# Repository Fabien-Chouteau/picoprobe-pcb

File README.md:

# picoprobe-pcb

If like me you love the Raspberry Pi Pico/RP2040, but your are not satisfied
with the available hardware debugging solution, this kit is for you ^^

This PCB is designed to turn a Pico into a nice debug probe using the
[PicoProbe software](https://github.com/raspberrypi/picoprobe).

Available at:

# Usage

## Mounting options

There are two ways to mount a Raspberry Pi Pico on the Picoprobe-PCB. You can
either solder it directly for a slim/compact result (right), or use header to
be able to re-use the Pico on other projects (left).

## Install the Picoprobe software

 1. Either get the picoprobe `.uf2` binary from our release [here](https://github.com/Fabien-Chouteau/picoprobe-pcb/releases/tag/v1.0) or compile
 it yourself from sources [here](https://github.com/raspberrypi/picoprobe).

 1. Hold the BOOTSEL button on the Pico, then connect to your computer using a
 micro USB cable.

 1. Drag and drop the UF2 file on to the RPI-RP2 drive.

 1. You should be good to go.

### Plug the picoprobe SWD pin to the Pico that you want to debug

### Build Raspberry Pi's openocd

```console
$ sudo apt install automake autoconf build-essential texinfo libtool libftdi-dev libusb-1.0-0-dev
$ git clone https://github.com/raspberrypi/openocd.git --branch picoprobe --depth=1 --no-single-branch
$ cd openocd
$ ./bootstrap
$ ./configure --enable-picoprobe
$ make -j4
```

### Run openocd

```console
$ ./src/openocd  -s tcl -f interface/picoprobe.cfg -f target/rp2040.cfg
Open On-Chip Debugger 0.10.0+dev-g18b4c35-dirty (2021-10-16-16:51)
Licensed under GNU GPL v2
For bug reports, read
        http://openocd.org/doc/doxygen/bugs.html
Info : only one transport option; autoselect 'swd'
Warn : Transport "swd" was already selected
adapter speed: 5000 kHz

Info : Hardware thread awareness created
Info : Hardware thread awareness created
Info : RP2040 Flash Bank Command
Info : Listening on port 6666 for tcl connections
Info : Listening on port 4444 for telnet connections
Info : clock speed 5000 kHz
Info : SWD DPIDR 0x0bc12477
Info : SWD DLPIDR 0x00000001
Info : SWD DPIDR 0x0bc12477
Info : SWD DLPIDR 0x10000001
Info : rp2040.core0: hardware has 4 breakpoints, 2 watchpoints
Info : rp2040.core1: hardware has 4 breakpoints, 2 watchpoints
Info : starting gdb server for rp2040.core0 on 3333
Info : Listening on port 3333 for gdb connections
Info : accepting 'gdb' connection on tcp/3333
Warn : target was in unknown state when halt was requested
target halted due to debug-request, current mode: Thread 
xPSR: 0x21000000 pc: 0x10008f64 msp: 0x20041fc0
Info : RP2040 B0 Flash Probe: 2097152 bytes @10000000, in 512 sectors
[...]
```

### Debug!

Now that openocd is connected, you can start debugging with GDB for instance.

```console
$ arm-eabi-none-gdb
(gdb) target extended-remote :3333
```

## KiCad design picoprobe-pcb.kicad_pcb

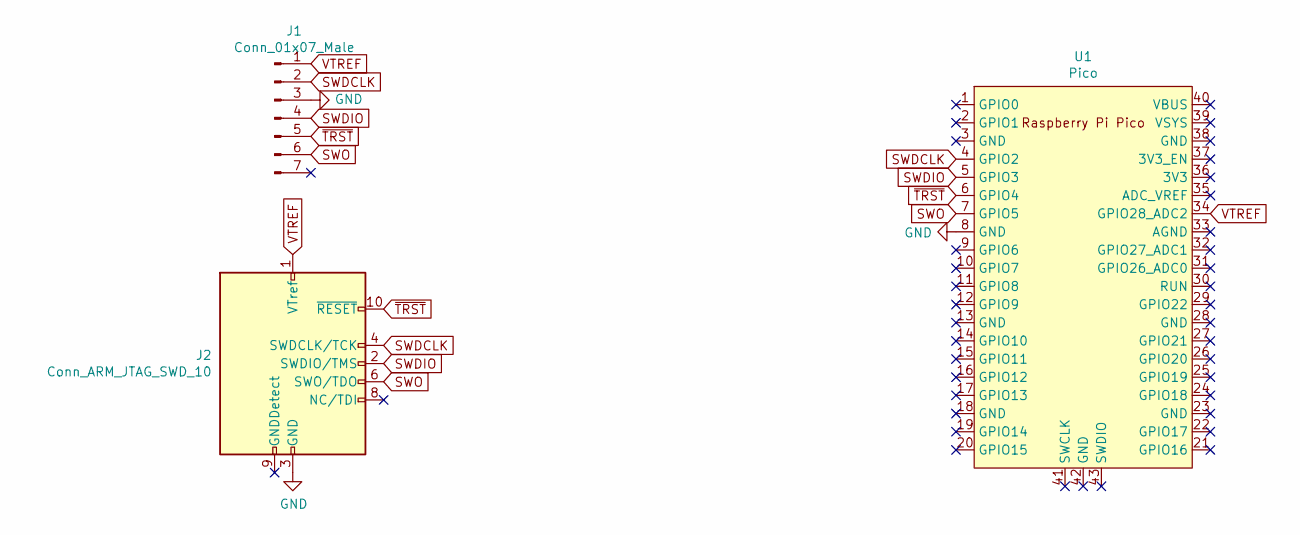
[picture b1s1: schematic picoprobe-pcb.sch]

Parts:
J1: Conn_01x07_Male; PinHeader_1x07_P2.54mm_Vertical
J2: Conn_ARM_JTAG_SWD_10; ARM_10_PIN_SMT
U1: Pico; RPi_Pico_SMD_TH

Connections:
GND: J1.3, J2.3 (GND), J2.5 (GND), U1.8 (GND)
SWDCLK: J1.2, J2.4 (SWDCLK/TCK), U1.4 (GPIO2)
SWDIO: J1.4, J2.2 (SWDIO/TMS), U1.5 (GPIO3)
SWO: J1.6, J2.6 (SWO/TDO), U1.7 (GPIO5)
VTREF: J1.1, J2.1 (VTref), U1.34 (GPIO28_ADC2)
~TRST: J1.5, J2.10 (~RESET~), U1.6 (GPIO4)

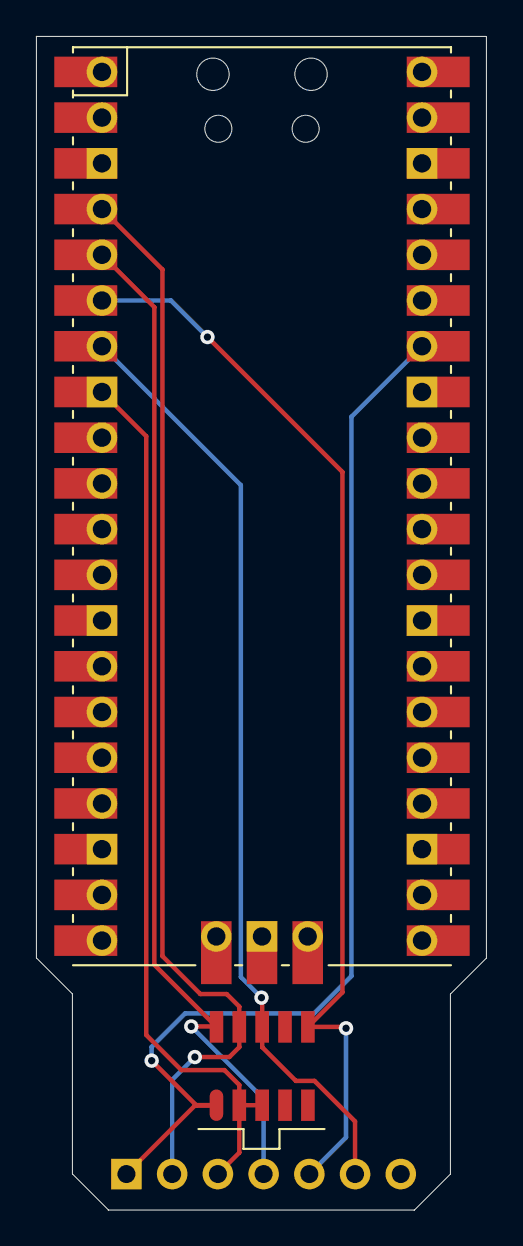
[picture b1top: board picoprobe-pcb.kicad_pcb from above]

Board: 2 copper layers, 25.0 x 65.2 mm, 3 parts (1 on the bottom side), 6 nets.

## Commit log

2021-10-17 rev-1.0
2021-12-09 Add some pictures
